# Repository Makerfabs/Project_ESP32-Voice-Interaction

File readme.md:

# ESP32 Voice Interaction

```c++
/*
Version:		V1.3
Author:			Vincent
Create Date:	2020/10/16

Note:
		2020/12/24 v1.3: Update readme.
		v1.2 Add Interphone example.
		v1.1 Add Record & Play example.
		
*/
```

[toc]

# Makerfabs

[Makerfabs home page](https://www.makerfabs.com/)

[Makerfabs Wiki](https://makerfabs.com/wiki/index.php?title=Main_Page)

# ESP32 Voice Interaction Hat

## Intruduce

Product Link ：[Voice Interaction Hat for Makepython](https://www.makerfabs.com/voice-interaction-hat-for-makepython.html) 

Wiki Link :  [Voice_Interaction_Hat_for_MakePython](https://wiki.makerfabs.com/Voice_Interaction_Hat_for_MaESP_ESP32.html) 

ESP32 Voice Interaction is an extended version with speakers and mics. The audio IC is WM8960. It has a button, SD card slot and a headphone jack.  It is convenient to produce MP3, interphone, recording pen and other items. 

The two functions of recording pen and walkie-talkie are realized. The recorder pen provides a simple menu for selecting play and recording. A UDP walkie-talkie can talk to any device under the same WIFI.

## Feature

- Micro SD card slot on board.

### Front:

### Back:

# Example

## Equipment list

- [MakePython ESP32](https://www.makerfabs.com/open-hardware/maboards/maesp.html)
- [MakaPython Voice Interaction Hat](https://www.makerfabs.com/voice-interaction-hat-for-makepython.html)
- Micro SD card (Part of the project)

## Compiler Options

**If you have any questions，such as how to install the development board, how to download the code, how to install the library. Please refer to :[Makerfabs_FAQ](https://github.com/Makerfabs/Makerfabs_FAQ)**

- Install board : ESP32 .
- Install library : Adafruit_GFX library.
- Install library : Adafruit SSD1306.

- Insert a Micro SD card into ESP32 Touch Camera.
- Upload codes, select "ESP32 Wrover Module" and "Huge APP"

## Example List

### ESP32_Record_Play
A recorder with a simple menu.

- Insert SD card.
- Upload code to ESP32.
- Restart ESP32.

### ESP32_Interphone
UDP protocol LAN walkie-talkie.

- Prepare two or more ESP32 and Voice Hat.
- Set WIFI ssid and password.
- Upload code to ESP32.
- Restart ESP32.
- Press the left button to speak, and others will play.

### wav_play
Test code, don't use. It can play wav file, but need a specific format.

### record
Record 5 second sound and playback.
- Insert SD card.
- Upload code to ESP32.
- Restart ESP32.
- Press the left button to start recording, recording will end at 5S.
- After the recording is over, the player will play the recording.

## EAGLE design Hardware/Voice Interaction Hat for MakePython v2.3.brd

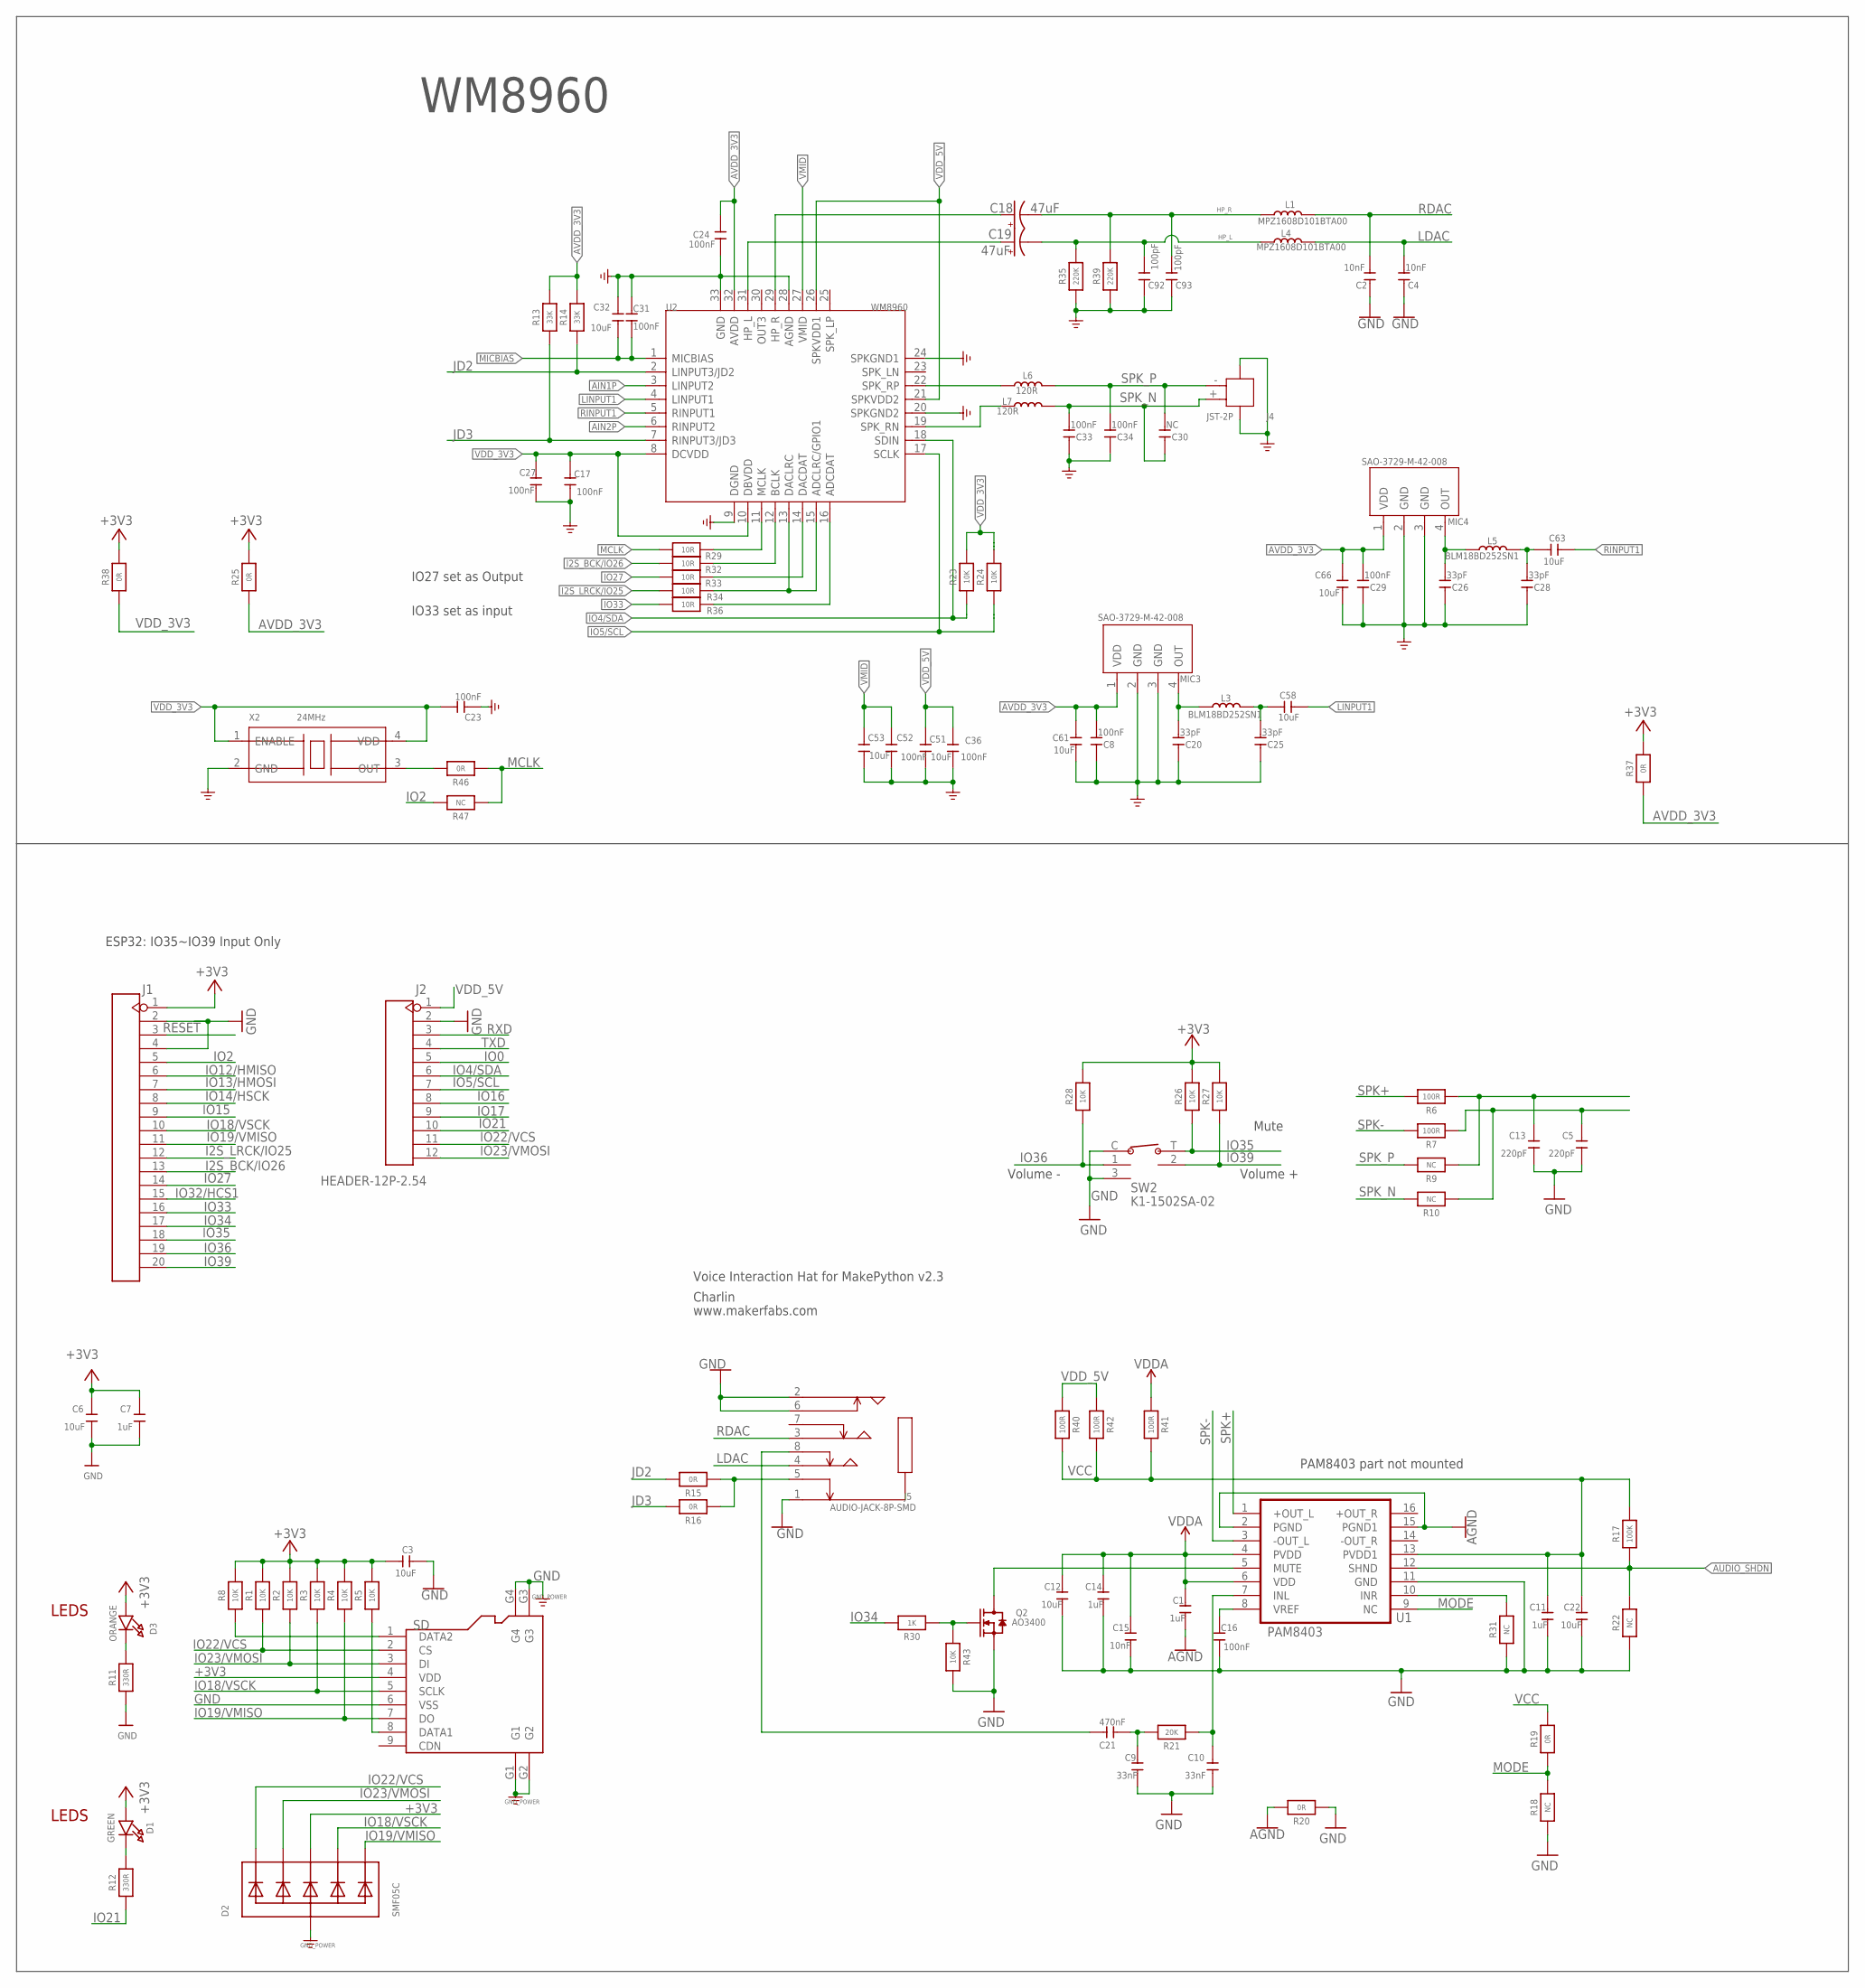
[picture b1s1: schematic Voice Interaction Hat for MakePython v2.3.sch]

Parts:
C1, C7, C11, C14: 1uF; DISCRETE_C0603
C2, C4: 10nF; C0402
C3, C6, C12, C22: 10uF; DISCRETE_C0603
C5, C13: 220pF; DISCRETE_C0603
C8, C29, C33, C34: 100nF; C0603
C9, C10: 33nF; DISCRETE_C0603
C15: 10nF; DISCRETE_C0603
C16: 100nF; DISCRETE_C0603
C17, C23, C24, C27, C31, C36, C52: 100nF; C0402
C18, C19: 47uF; EIA3528
C20, C25, C26, C28: 33pF; C0603
C21: 470nF; DISCRETE_C0603
C30: NC; C0603
C32, C51, C53, C58, C61, C63, C66: 10uF; C0603
C92, C93: 100pF; C0402
D1: GREEN; CHIPLED_0805_NOOUTLINE
D2: SMF05C; SOT363
D3: ORANGE; CHIPLED_0805_NOOUTLINE
J1: HEADER-20P-2.54; 20P-2.54
J2: HEADER-12P-2.54; 12P-2.54
J4: JST-2P; HW2-SMD-2.0-90D
J5: AUDIO-JACK-8P-SMD; AUDIO8P-SMD-3.5-14.5X6.1X4.0MM
L1, L4: MPZ1608D101BTA00; L0603
L3, L5: BLM18BD252SN1; L0603
L6, L7: 120R; L0603
MIC3, MIC4: SAO-3729-M-42-008; MIC4-SMD-3.76X2.95MM
Q2: AO3400; SOT23@1
R1, R2, R3, R4, R5, R8, R23, R24, R26, R27, R28, R43: 10K; 0603-NO
R6, R7, R40, R41, R42: 100R; 0603-NO
R9, R10, R18, R22, R31, R47: NC; 0603-NO
R11, R12: 330R; 0603-NO
R13, R14: 33K; 0603-NO
R15, R16, R19, R20, R25, R37, R38, R46: 0R; 0603-NO
R17: 100K; 0603-NO
R21: 20K; 0603-NO
R29, R32, R33, R34, R36: 10R; 0603-NO
R30: 1K; 0603-NO
R35, R39: 220K; 0603-NO
SD: HOLDER-MICROSD-9P; 9P-SMD-W/-RING
SW2: K1-1502SA-02; SMD5-60P-1180L1170W
U1: PAM8403; SOP-16
U2: WM8960; QFN32G-0.5-5X5MM
X2: 24MHz; OSC4-SMD-2.5X2.0X0.8MM

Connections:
$123: C18.A (+), U2.29 (HP_R)
$124: C19.A (+), U2.31 (HP_L)
+3V3: C3.2, C6.2, C7.2, D1.A, D2.4 (C3), D3.A, J1.1, R1.2, R2.2, R3.2, R4.2, R5.2, R8.2, R25.2, R26.2, R27.2, R28.2, R37.2, R38.2, SD.4 (VDD)
AGND: C1.1, R20.2, U1.2 (PGND), U1.15 (PGND1)
AIN1P: U2.3 (LINPUT2)
AIN2P: U2.6 (RINPUT2)
AUDIO_SHDN: R17.1, R22.2, U1.12 (SHND)
AVDD_3V3: C8.1, C24.2, C29.1, C61.2, C66.2, MIC3.1 (VDD), MIC4.1 (VDD), R13.2, R14.2, R25.1, R37.1, U2.32 (AVDD)
GND: C2.1, C3.1, C4.1, C5.1, C6.1, C7.1, C8.2, C9.1, C10.1, C11.1, C12.1, C13.1, C14.1, C15.1, C16.1, C17.1, C20.2, C22.1, C23.1, C24.1, C25.2, C26.2, C27.1, C28.2, C29.2, C31.2, C32.1, C33.2, C34.2, C36.1, C51.2, C52.1, C53.2, C61.1, C66.1, C92.1, C93.1, D2.2 (A), J1.2, J1.4, J2.2, J4.3, J4.4, J5.1, J5.2, J5.6, MIC3.2 (GND), MIC3.3 (GND), MIC4.2 (GND), MIC4.3 (GND), Q2.2 (S), R11.1, R18.1, R20.1, R22.1, R31.1, R35.1, R39.1, R43.2, SD.6 (VSS), SD.G1, SD.G2, SD.G3, SD.G4, SW2.3, SW2.C, U1.11 (GND), U2.9 (DGND), U2.20 (SPKGND2), U2.24 (SPKGND1), U2.28 (AGND), U2.33 (GND), X2.2 (GND)
HP_L: C19.C (-), C92.2, L4.1, R35.2
HP_R: C18.C (-), C93.2, L1.1, R39.2
I2S_BCK/IO26: J1.13, R32.2
I2S_LRCK/IO25: J1.12, R34.2
IO0: J2.5
IO2: J1.5, R47.2
IO4/SDA: J2.6, R23.1, U2.18 (SDIN)
IO5/SCL: J2.7, R24.1, U2.17 (SCLK)
IO12/HMISO: J1.6
IO13/HMOSI: J1.7
IO14/HSCK: J1.8
IO15: J1.9
IO16: J2.8
IO17: J2.9
IO18/VSCK: D2.5 (C4), J1.10, R3.1, SD.5 (SCLK)
IO19/VMISO: D2.6 (C5), J1.11, R4.1, SD.7 (DO)
IO21: J2.10, R12.1
IO22/VCS: D2.1 (C1), J2.11, R1.1, SD.2 (CS)
IO23/VMOSI: D2.3 (C2), J2.12, R2.1, SD.3 (DI)
IO27: J1.14, R33.2
IO32/HCS1: J1.15
IO33: J1.16, R36.2
IO34: J1.17, R30.2
IO35: J1.18, R26.1, SW2.T
IO36: J1.19, R28.1, SW2.1
IO39: J1.20, R27.1, SW2.2
JD2: R14.1, R15.2, U2.2 (LINPUT3/JD2)
JD3: R13.1, R16.2, U2.7 (RINPUT3/JD3)
LDAC: C4.2, J5.4, L4.2
LINPUT1: C58.2, U2.4 (LINPUT1)
MCLK: R29.2, R46.1, R47.1
MICBIAS: C31.1, C32.2, U2.1 (MICBIAS)
MODE: R18.2, R19.1, U1.9 (NC)
unnamed: R8.1, SD.1 (DATA2)
unnamed: R5.1, SD.8 (DATA1)
unnamed: D1.C, R12.2
unnamed: C10.2, R21.1, U1.7 (INL)
unnamed: D3.C, R11.2
unnamed: C13.2, R6.1, R9.1
unnamed: C9.2, C21.1, R21.2
unnamed: Q2.1 (G), R30.1, R43.1
unnamed: J5.5, R15.1, R16.1
unnamed: R33.1, U2.14 (DACDAT)
unnamed: Q2.3 (D), U1.5 (MUTE)
unnamed: C25.1, C58.1, L3.2
unnamed: C20.1, L3.1, MIC3.4 (OUT)
unnamed: C5.2, R7.1, R10.1
unnamed: C28.1, C63.1, L5.2
unnamed: C16.2, U1.8 (VREF)
unnamed: R46.2, X2.3 (OUT)
unnamed: R31.2, U1.10 (INR)
unnamed: C26.1, L5.1, MIC4.4 (OUT)
unnamed: R36.1, U2.16 (ADCDAT)
unnamed: R34.1, U2.13 (DACLRC), U2.15 (ADCLRC/GPIO1)
unnamed: R32.1, U2.12 (BCLK)
unnamed: R29.1, U2.11 (MCLK)
unnamed: L6.1, U2.22 (SPK_RP)
unnamed: L7.1, U2.19 (SPK_RN)
unnamed: C21.2, J5.8
RDAC: C2.2, J5.3, L1.2
RESET: J1.3
RINPUT1: C63.2, U2.5 (RINPUT1)
RXD: J2.3
SPK+: R6.2, U1.1 (+OUT_L)
SPK-: R7.2, U1.3 (-OUT_L)
SPK_N: C30.2, C33.1, J4.+ (1), L7.2, R10.2
SPK_P: C30.1, C34.1, J4.- (2), L6.2, R9.2
TXD: J2.4
VCC: C11.2, C22.2, R17.2, R19.2, R40.2, R41.2, R42.2, U1.13 (PVDD1)
VDDA: C1.2, C12.2, C14.2, C15.2, R41.1, U1.4 (PVDD), U1.6 (VDD)
VDD_3V3: C17.2, C23.2, C27.2, R23.2, R24.2, R38.1, U2.8 (DCVDD), U2.10 (DBVDD), X2.1 (ENABLE), X2.4 (VDD)
VDD_5V: C36.2, C51.1, J2.1, R40.1, R42.1, U2.21 (SPKVDD2), U2.26 (SPKVDD1)
VMID: C52.2, C53.1, U2.27 (VMID)

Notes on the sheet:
ESP32: IO35~IO39 Input Only
Voice Interaction Hat for MakePython v2.3
LEDS
Charlin
Volume +
Volume -
Mute
www.makerfabs.com
WM8960
IO27 set as Output
IO33 set as input
PAM8403 part not mounted

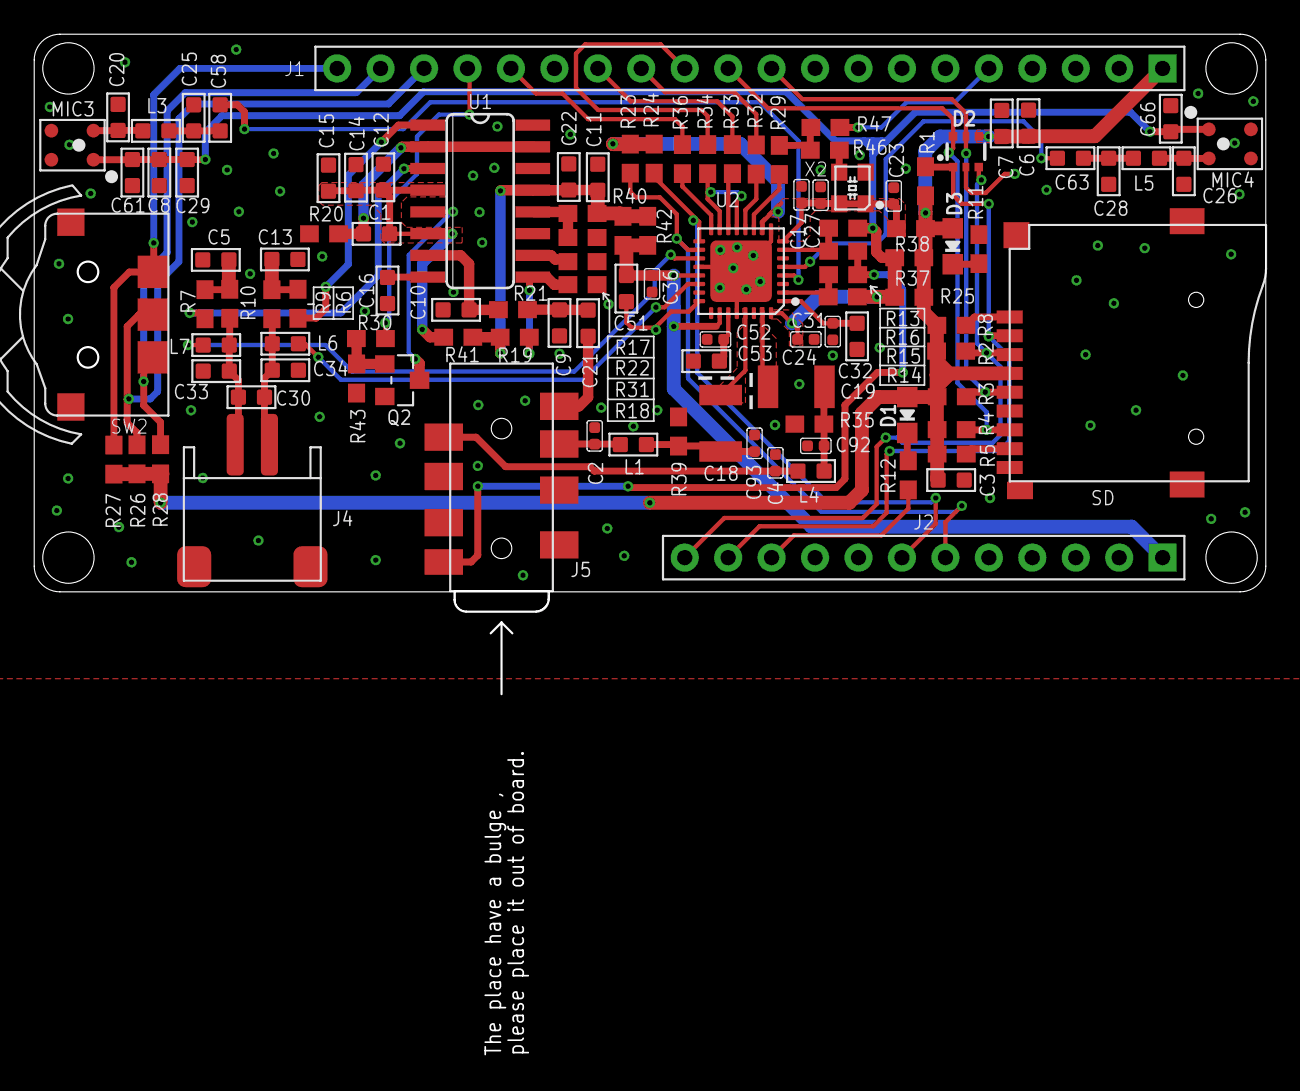
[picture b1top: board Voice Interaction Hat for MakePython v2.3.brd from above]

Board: 2 copper layers, 72.0 x 32.6 mm, 111 parts (1 on the bottom side), 69 nets.

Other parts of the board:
U$1: MAKERFABS_0.3

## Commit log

2020-10-16 Record and play
2020-10-20 wm8960 reday
2020-11-02 updata1102
2020-11-17 add interphone example
2020-12-19 V2.3
    Schematic and PCB
2020-12-22 modify 20201222
2020-12-24 Change wrong directory name
2021-03-17 comment alarm()
2021-05-08 Add picture

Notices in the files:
parts and their libraries:
microbuilder: This work is placed in the public domain, and may be freely used for commercial and non-commercial work with the following conditions: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
SparkFun-Capacitors: Licensing: Creative Commons ShareAlike 4.0 International - https://creativecommons.org/licenses/by-sa/4.0
